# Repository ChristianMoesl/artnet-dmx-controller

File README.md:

# ArtNet DMX Controller
This is a small LED controller for DMX LED spots, which can be accessed and controlled through the ArtNet protocol over Ethernet.

## Assembled PCB

##  LICENSE
The contents of this repository are covered under the [MIT License](./LICENSE).

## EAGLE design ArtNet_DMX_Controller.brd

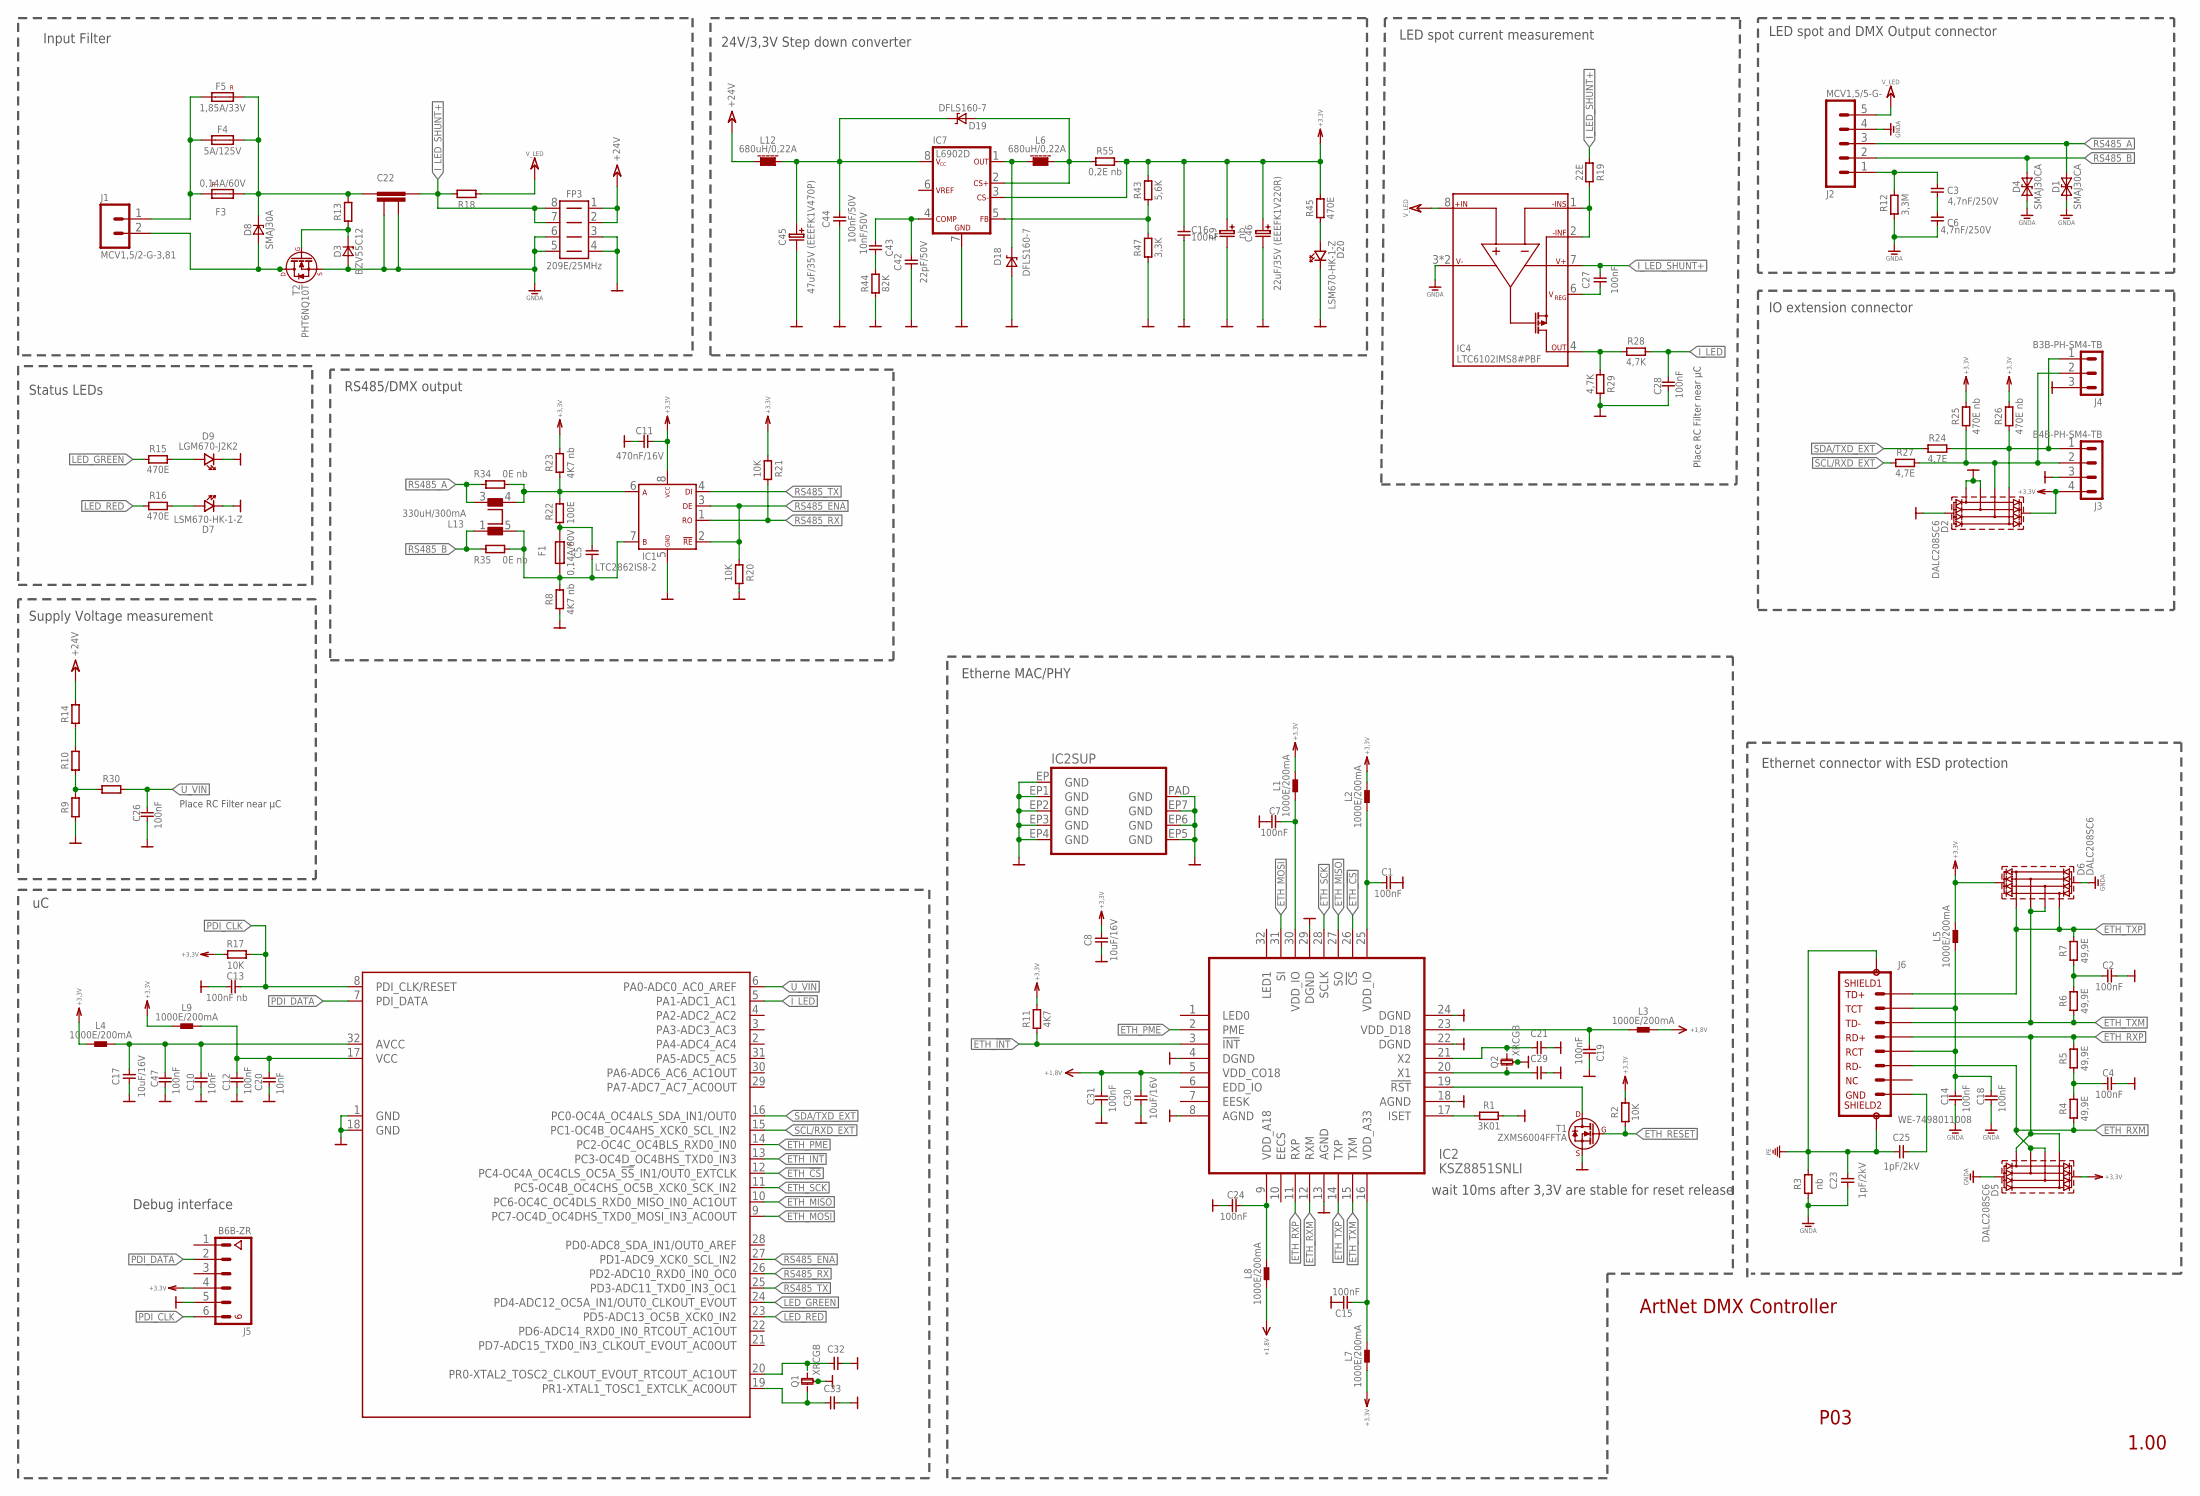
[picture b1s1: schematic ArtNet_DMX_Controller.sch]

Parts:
C1, C2, C4, C7, C12, C14, C15, C16, C18, C19, C24, C26, C28, C31, C47: 100nF; 0603
C3, C6: 4,7nF/250V; 2220
C5: C-0805; 0805
C8, C17, C30: 10uF/16V; 0805
C9: nb; 6032
C10, C20: 10nF; 0603
C11: 470nF/16V; 0603
C13: 100nF nb; 0603
C21, C29, C32, C33: C-0603; 0603
C22: NFM55P
C23, C25: 1pF/2kV; 1206
C27: 100nF; 0805
C42: 22pF/50V; 0603
C43: 10nF/50V; 0603
C44: 100nF/50V; 0805
C45: 47uF/35V (EEEFK1V470P); PANASONIC-SIZE-CODE-D
C46: 22uF/35V (EEEFK1V220R); PANASONIC-SIZE-CODE-D
D1, D4: SMAJ30CA; DO-214AC
D2, D5, D6: DALC208SC6; SOT23-6L
D3: BZV55C12; SOD80C
D7, D20: LSM670-HK-1-Z; M670
D8: SMAJ30A; DO-214AC
D9: LGM670-J2K2; M670
D18, D19: DFLS160-7; POWERDI123
F1, F3: 0,14A/60V; 1812L
F4: 5A/125V; 6.1X2.69MM
F5: 1,85A/33V; 2920L
FP3: 209E/25MHz; WE-MLS-10,88MMX5,49MM
IC1: LTC2862IS8-2; SO8
IC2: KSZ8851SNLI; QFN32_5X5
IC3: E5-TQFP; TQFP32
IC4: LTC6102IMS8#PBF; MS8
IC7: L6902D; SO8
J1: MCV1,5/2-G-3,81
J2: MCV1,5/5-G-; MCV1,5/5-G-3,81_MOD
J3: B4B-PH-SM4-TB
J4: B3B-PH-SM4-TB
J5: B6B-ZR
J6: WE-7498011008; WE-749801108
L1, L2, L3, L4, L5, L7, L8, L9: 1000E/200mA; 0603
L6, L12: 680uH/0,22A; 73XX
L13: 330uH/300mA; WE-SL1
Q1, Q2: XRCGB
R1: 3K01; 0603
R2, R17, R20, R21: 10K; 0603
R3: nb; 1206
R4, R5, R6, R7: 49,9E; 0603
R8, R23: 4K7 nb; 0805
R9, R10, R14, R30: R-0603; 0603
R11: 4K7; 0603
R12: 3,3M; 0207
R13: R-0805; 0805
R15, R16, R45: 470E; 0603
R18: R-2512; 2512
R19: 22E; 0603
R22: 100E; 0207
R24, R27: 4,7E; 0603
R25, R26: 470E nb; 0603
R28, R29: 4,7K; 0603
R34, R35: 0E nb; 0805
R43: 5,6K; 0603
R44: 82K; 0603
R47: 3,3K; 0603
R55: 0,2E nb; 0805
T1: ZXMS6004FFTA; SOT-23
T2: PHT6NQ10T; SOT223

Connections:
+1,8V: C30.2, C31.2, IC2.5 (VDD_CO18), L3.2, L8.1
+3,3V: C8.1, C9.PLUS (+), C11.2, C16.2, C46.+, D2.2 (REF2), D5.2 (REF2), D6.2 (REF2), IC1.8 (VCC), IC7.3 (CS-), J3.4, J5.4, L1.2, L2.2, L4.1, L5.2, L7.1, L9.1, R2.2, R11.2, R17.2, R21.2, R23.2, R25.2, R26.2, R43.2, R45.2, R55.2
+24V: FP3.1, FP3.2, L12.1, R14.2
AVCC: C10.2, C17.2, C47.2, IC3.32 (AVCC), L4.2
BLA: C5.1, F1.1, IC1.7 (B), L13.5 (2), R8.2, R35.2
BLA2: IC1.6 (A), L13.4 (3), R22.2, R23.1, R34.2
ETH_!CS: IC2.26 (!CS), IC3.12 (PC4-OC4A_OC4CLS_OC5A_!SS!_IN1/OUT0_EXTC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)
ETH_!INT: IC2.3 (!INT), IC3.13 (PC3-OC4D_OC4BHS_TXD0_IN3), R11.1
ETH_MISO: IC2.27 (SO), IC3.10 (PC6-OC4C_OC4DLS_RXD0_MISO_IN0_AC1OUT)
ETH_MOSI: IC2.31 (SI), IC3.9 (PC7-OC4D_OC4DHS_TXD0_MOSI_IN3_AC0OUT)
ETH_PME: IC2.2 (PME), IC3.14 (PC2-OC4C_OC4BLS_RXD0_IN0)
ETH_RESET: R2.1, T1.1 (G)
ETH_RXM: D5.3 (I/O2), D5.4 (I/O3), IC2.12 (RXM), J6.P$6 (RD-), R4.1
ETH_RXP: D5.1 (I/O1), D5.6 (I/O4), IC2.11 (RXP), J6.P$3 (RD+), R5.2
ETH_SCK: IC2.28 (SCLK), IC3.11 (PC5-OC4B_OC4CHS_OC5B_XCK0_SCK_IN2)
ETH_TXM: D6.3 (I/O2), D6.4 (I/O3), IC2.15 (TXM), J6.P$2 (TD-), R6.1
ETH_TXP: D6.1 (I/O1), D6.6 (I/O4), IC2.14 (TXP), J6.P$1 (TD+), R7.2
GND: C1.2, C2.2, C4.2, C7.2, C8.2, C9.MINUS (-), C10.1, C11.1, C12.1, C13.2, C15.2, C16.1, C17.1, C19.2, C20.1, C21.2, C24.1, C26.1, C28.1, C29.2, C30.1, C31.1, C32.2, C33.2, C42.1, C44.1, C45.-, C46.-, C47.1, D2.1 (I/O1), D2.3 (I/O2), D2.5 (REF1), D7.K, D9.K, D18.A, D20.K, FP3.3, FP3.4, IC1.5 (GND), IC2.4 (DGND), IC2.8 (AGND), IC2.13 (AGND), IC2.18 (AGND), IC2.22 (DGND), IC2.24 (DGND), IC2.29 (DGND), IC2.EP (GND), IC2.EP1 (GND), IC2.EP2 (GND), IC2.EP3 (GND), IC2.EP4 (GND), IC2.EP5 (GND), IC2.EP6 (GND), IC2.EP7 (GND), IC2.PAD (GND), IC3.1 (GND), IC3.18 (GND), IC7.7 (GND), J3.3, J4.3, J5.5, Q1.3, Q1.4, Q2.3, Q2.4, R1.2, R8.1, R9.1, R20.1, R29.2, R44.1, R47.1, T1.2 (S)
GNDA: C6.P$1 (1), C14.1, C18.1, C22.3, C22.4, C23.1, D1.K (2), D3.A, D4.K (2), D5.5 (REF1), D6.5 (REF1), FP3.5, FP3.6, IC4.3 (V-), IC4.5 (V-), J2.4, R3.1, R12.1, T2.3 (S)
I_LED: C28.2, IC3.5 (PA1-ADC1_AC1), R28.2
I_LED_SHUNT+: C22.2, C27.2, FP3.7, FP3.8, IC4.7 (V+), R18.2, R19.1
LED_GREEN: IC3.24 (PD4-ADC12_OC5A_IN1/OUT0_CLKOUT_EVOUT), R15.1
LED_RED: IC3.23 (PD5-ADC13_OC5B_XCK0_IN2), R16.1
unnamed: IC2.17 (ISET), R1.1
unnamed: C3.P$2 (2), J2.1, R12.2
unnamed: IC2.19 (!RST), T1.3 (D)
unnamed: C7.1, IC2.30 (VDD_IO), L1.1
unnamed: C1.1, IC2.25 (VDD_IO), L2.1
unnamed: C5.2, F1.2, R22.1
unnamed: D3.K, R13.1, T2.1 (G)
unnamed: C27.1, IC4.6 (VREG)
unnamed: C3.P$1 (1), C6.P$2 (2)
unnamed: C25.2, J6.P$8 (GND)
unnamed: D9.A, R15.2
unnamed: D7.A, R16.2
unnamed: C29.1, IC2.20 (X1), Q2.1
unnamed: C32.1, IC3.20 (PR0-XTAL2_TOSC2_CLKOUT_EVOUT_RTCOUT_AC1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), Q1.2
unnamed: F3.2, F4.1, F5.1, J1.1
unnamed: C33.1, IC3.19 (PR1-XTAL1_TOSC1_EXTCLK_AC0OUT), Q1.1
unnamed: R10.2, R14.1
unnamed: IC4.4 (OUT), R28.1, R29.1
unnamed: C22.1, D8.K, F3.1, F4.2, F5.2, R13.2
unnamed: C15.1, IC2.16 (VDD_A33), L7.2
unnamed: R9.2, R10.1, R30.1
unnamed: D2.6 (I/O4), J3.1, J4.1, R24.2, R26.1
unnamed: C21.1, IC2.21 (X2), Q2.2
unnamed: D2.4 (I/O3), J3.2, J4.2, R25.1, R27.2
unnamed: C14.2, C18.2, J6.P$4 (TCT), J6.P$5 (RCT), L5.1
unnamed: C2.1, R6.2, R7.1
unnamed: C24.2, IC2.9 (VDD_A18), L8.2
unnamed: D8.A, J1.2, T2.2 (D), T2.4 (D1)
unnamed: C4.1, R4.2, R5.1
unnamed: IC4.1 (-INS), IC4.2 (-INF), R19.2
unnamed: IC7.5 (FB), R43.1, R47.2
unnamed: D19.A, IC7.2 (CS+), L6.2, R55.1
unnamed: D18.K, IC7.1 (OUT), L6.1
unnamed: C42.2, C43.1, IC7.4 (COMP)
unnamed: C43.2, R44.2
unnamed: D20.A, R45.1
unnamed: C44.2, C45.+, D19.K, IC7.8 (VCC), L12.2
PDI_CLK: C13.1, IC3.8 (PDI_CLK/RESET), J5.6, R17.1
PDI_DATA: IC3.7 (PDI_DATA), J5.2
PE: C23.2, C25.1, J6.P$9 (9), J6.P$10 (10), R3.2
RS485_A: D1.A (1), J2.3, L13.3 (4), R34.1
RS485_B: D4.A (1), J2.2, L13.1, R35.1
RS485_ENA: IC1.2 (/RE), IC1.3 (DE), IC3.27 (PD1-ADC9_XCK0_SCL_IN2), R20.2
RS485_RX: IC1.1 (R0), IC3.26 (PD2-ADC10_RXD0_IN0_OC0), R21.1
RS485_TX: IC1.4 (DI), IC3.25 (PD3-ADC11_TXD0_IN3_OC1)
SCL/RXD_EXT: IC3.15 (PC1-OC4B_OC4AHS_XCK0_SCL_IN2), R27.1
SDA/TXD_EXT: IC3.16 (PC0-OC4A_OC4ALS_SDA_IN1/OUT0), R24.1
U_VIN: C26.2, IC3.6 (PA0-ADC0_AC0_AREF), R30.2
VCC: C12.2, C20.2, IC3.17 (VCC), L9.2
VDD_D18: C19.1, IC2.23 (VDD_D18), L3.1
V_LED: IC4.8 (+IN), J2.5, R18.1

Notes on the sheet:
wait 10ms after 3,3V are stable for reset release
Place RC Filter near µC
Supply Voltage measurement
Debug interface
Input Filter
Status LEDs
RS485/DMX output
24V/3,3V Step down converter
LED spot current measurement
LED spot and DMX Output connector
IO extension connector
Ethernet connector with ESD protection
Etherne MAC/PHY
ArtNet DMX Controller
P03
1.00

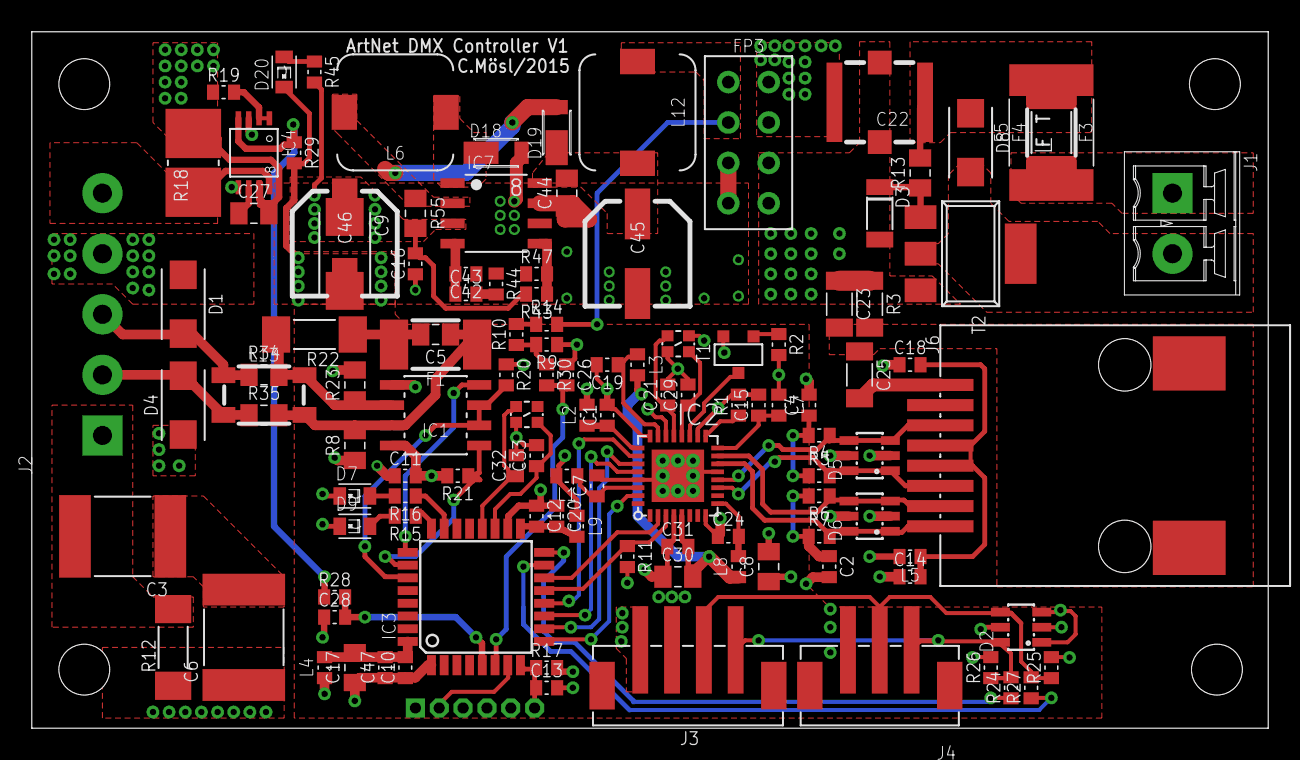
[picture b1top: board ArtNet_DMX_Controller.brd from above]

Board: 4 copper layers, 77.8 x 43.8 mm, 119 parts (1 on the bottom side), 74 nets.
